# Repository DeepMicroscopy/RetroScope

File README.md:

<picture>
  <source media="(prefers-color-scheme: dark)" srcset="retroscope/qml/icons/app_logo_dark.png">
  <source media="(prefers-color-scheme: light)" srcset="retroscope/qml/icons/app_logo_light.png">
  
</picture>

---

**An Open Framework for Motorizing and Digitizing Vintage Microscopes**

RetroScope is an open-source framework for older analog microscopes. It combines software, digital imaging, motorized stage and focus control, calibration workflows, and adaptable mechanical parts so that existing microscopes can be upgraded instead of replaced.

The project was developed as part of the master's thesis **"Retrofitting a Vintage Microscope: Development of an Embedded System for Motorized Control and Digital Imaging"** in Applied Computer Science at Flensburg University of Applied Sciences.

## Overview

RetroScope is not just a single application. It is intended as a complete retrofit framework:

- **Control software**: Python/PySide6 backend with a QML touchscreen interface.
- **Embedded system**: Raspberry Pi-based embedded system with mock/development support for desktop.
- **Motor control**: XY stage and Z focus movement through a motor controller ([Sangaboard](https://build.openflexure.org/openflexure-microscope/v7.0.0-beta5/parts/electronics/sangaboard.html)).
- **Digital imaging**: Live camera preview, snapshots, video recording, OME-TIFF support and gallery management.
- **Automation**: Autofocus, focus stacking and tile scanning with stitching support.
- **REST API**: FastAPI with Swagger/OpenAPI documentation for e.g. external tools.
- **Calibration**: Calibration wizards with objective profiles, pixel scale, stage scale, backlash compensation, etc.
- **Electronics**: PCB schematics and Gerber files for manufacturing. Optional, just used to reduce the amount of cabling.
- **Mechanical design**: Parametric Fusion/CAD files and 3D-printable parts for adapting the retrofit to different microscopes.

## Features

- Low-latency live microscope view with overlays such as crosshair, scale bar and grid.
- Objective profile system for different magnifications and numerical apertures.
- Camera-assisted calibration for image scale, stage scale, and backlash compensation
- Manual stage and focus control through touchscreen, joystick, and configurable buttons.
- Contract-based autofocus.
- Automated focus stacks and tile scans.
- Measurement tools for distances, rectangles and angles.
- Gallery for snapshots, videos, focus stacks, scans, and tagging.
- REST API to access captures and trigger actions like autofocus.
- Configurable dark/light UI
- Mock mode for development without microscope hardware.

## Screenshots

## Software Architecture

The software is organized into modular layers:

- `retroscope/drivers`: Low-level hardware drivers for camera input, Sangaboard motor control, joystick ADC, buttons, and endstop.
- `retroscope/services`: Application logic for motion, autofocus, calibration, camera processing, tile scanning, focus stacking, updates, ...
- `retroscope/api`: FastAPI REST interface and OpenAPI/Swagger documentation.
- `retroscope/domain`: Pure domain modules (+ calculations) for scan planning, focus metrics, objective calibration, measurement, ...
- `retroscope/bridge`: Qt/PySide bridge objects that expose APIs to QML.
- `retroscope/qml`: Touchscreen user interface components and views.
- `tests`: Unit tests for calibration, autofocus, motion, scanning, settings, ...

This separation enables the expansion of individual subsystems without rewriting the entire platform.

## Hardware Recommendations

The following parts were used for the prototype:

- Raspberry Pi 4 Model B, 4 GB RAM
- [Sangaboard](https://build.openflexure.org/openflexure-microscope/v7.0.0-beta5/parts/electronics/sangaboard.html)
- 3x 28BYJ-48 Stepper Motors
- DSI Capacitive Touch Display
- Analog Joystick with 10k Potentiometers
- ADS1115 ADC Modul
- Incremental Rotary Encoder
- Bearing (60mm * 78mm * 10mm)
- Endstop
- 4x Buttons
- Various cables
- ABS (& PETG) filament/s for 3D printed parts
- Optional Custom PCB

## Installation

Clone the repository and create a virtual environment:

```bash
git clone https://github.com/marvincarstensen/RetroScope.git
cd retroscope
python[3] -m venv .venv
source .venv/bin/activate
pip install -r requirements.txt
```

For Raspberry Pi deployment, an additional setup script, to e.g. setup the service, has to be run with sudo:
```bash
sudo bash deploy/setup.sh
```

## Running

Start the application:

```bash
python app.py
```
> [!NOTE]
> First launch may take a little longer while Python builds its caches.

Run in mock mode for desktop env:

```bash
python app.py --mock
```

Enable development mode with QML hot reloading:

```bash
python app.py --mock --dev
```

Apply a UI scale factor:

```bash
python app.py --scale 1.5
```

On the Raspberry Pi with Wayland:

```bash
WAYLAND_DISPLAY=wayland-0 XDG_RUNTIME_DIR=/run/user/1000 python app.py --scale=1.5
```

## Testing

Run the test suite:

```bash
.venv/bin/python -m pytest -q
```

Compile-check on the package:

```bash
.venv/bin/python -m compileall -q retroscope
```

Run QML lint checks:

```bash
.venv/bin/pyside6-qmllint -I retroscope/qml $(find retroscope/qml -name '*.qml')
```

## Evaluation

The evaluations run inside the main application so they use the real camera pipeline, motion
services, calibration state, and workflow services. Results are written as CSV files to
`evaluation_output/`, with per-trial rows followed by summary rows. Needs a textured specimen and a safe stage position to run properly. The active objective needs to be selected and calibrated before running measurements.

Available evaluation types:

- `motion_accuracy`: compares commanded X/Y movement with measured image displacement and backlash residuals.
- `stage_scale`: measures repeated stage-scale estimates in micrometres per motor step.
- `calibration_repeat`: repeats stage-scale and backlash checks for the active objective.
- `workflow_reliability`: runs autofocus, focus stacking, and tile scanning through the app services.

Example runs:

```bash
python app.py --eval motion_accuracy --eval-arg axes=xy --eval-arg steps=100,200 --eval-arg reps=10
python app.py --eval stage_scale --eval-arg steps=100 --eval-arg reps=10
python app.py --eval calibration_repeat --eval-arg stage_steps=200 --eval-arg reps=10
python app.py --eval workflow_reliability --eval-arg reps=10 --eval-arg workflows=autofocus,focus_stacking,tile_scanning
```

## REST API

By default, the API is enabled and listens on port `8765`:

- `http://127.0.0.1:8765` / `http://<device-ip>:8765`
- Swagger UI: `http://<device-ip>:8765/docs`
- OpenAPI JSON: `http://<device-ip>:8765/openapi.json`

The current API is intentionally small and intended as an extension point for scripts, notebooks, and external tools.

Endpoint                                  | Description
------------------------------------------|-------------------------------
`GET /api/v1/health`                      | API health check.
`GET /api/v1/captures`                    | List gallery captures.
`GET /api/v1/captures/{id}/download`      | Download the original capture file.
`POST /api/v1/actions/autofocus`          | Start autofocus.
`POST /api/v1/actions/capture`            | Start capture.

## Demo Notebook

The repository contains a basic Jupyter notebook, `retroscope_api_demo.ipynb`, that demonstrates how to use the REST API.

## Shortcuts (Mock only)

The following keyboard shortcuts can be used in mock simulation:

Key       | Function           
----------|-------------------
WASD      | Joystick axes        
Space     | Joystick center (release)         
+/-       | Encoder step +-1       
1/2/3/4   | Button press 0–3      
E         | Simulate endstop triggered/released toggle

## Dependencies

The following plugins, libraries and frameworks are used:

Name                    | Version           
------------------------|-------------------
PySide6                 | 6.11.1
fastapi                 | 0.136.3
httpx2                  | 2.3.0
uvicorn                 | 0.49.0
numpy                   | 2.4.6
pytest                  | 9.0.3
opencv-python-headless  | 4.13.0.92
Pillow                  | 12.2.0
tifffile                | 2026.5.15
sangaboard              | 0.3.3
smbus2 (only on Pi)     | 0.6.1           
gpiod (only on Pi)      | 2.4.2   

## Additional Sources

- Font Awesome by Dave Gandy (https://fontawesome.com/)
- LateX Template, Logo & CI (DeepMicroscopy) by Nils Porsche

## Declaration: Use of Generative AI

The following generative AI tools were used in this thesis: 

- GitHub Copilot in VS Code was used for inline code-completion suggestions during implementation and writing.
- ChatGPT (OpenAI) & Claude (Anthropic) used to support brainstorming, quick research, and the generation of selected parts of the code (e.g. unit tests). AI-assisted scripts and functions are marked in the source code via comments.
- DeepL write (DeepL SE) were used in language editing and grammatical proof-reading.

All AI-generated material was critically reviewed, edited, and verified by the author. No generative AI system was used to produce original scientific results, experimental data, proofs, or final implementations of algorithms. The author assumes full responsibility for the content, correctness, and originality of this thesis.

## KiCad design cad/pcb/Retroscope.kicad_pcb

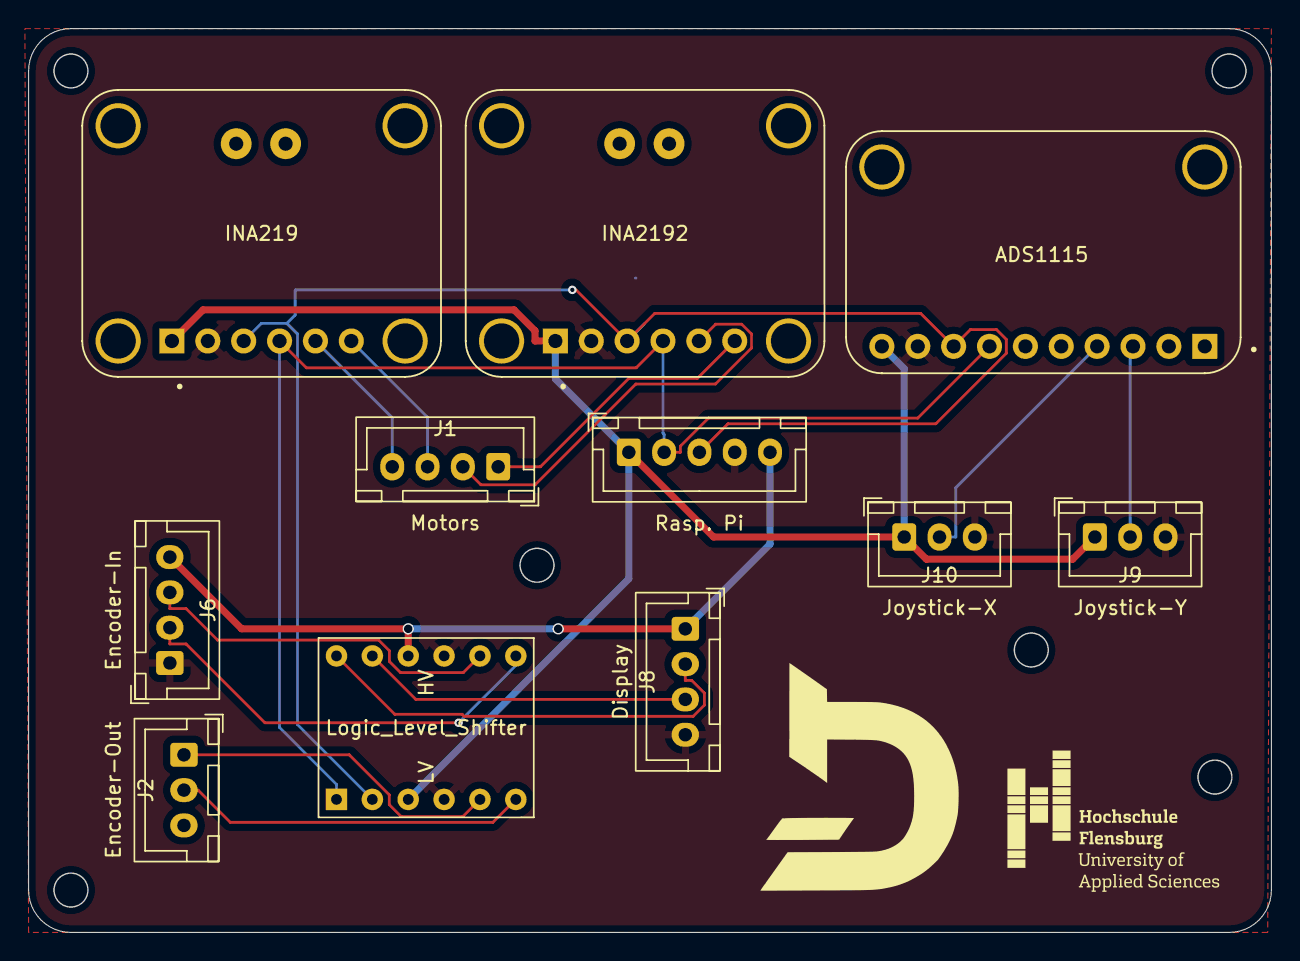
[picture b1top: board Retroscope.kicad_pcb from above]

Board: 2 copper layers, 88.0 x 64.0 mm, 11 parts (0 on the bottom side), 19 nets.

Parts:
A1: Logic_Level_Shifter; LogicLevelConverter_Module
ADS1115: ZC261500; MODULE_ZC261500
INA219, INA2192: INA219; MODULE_INA219
J1: Motors; JST_XH_B4B-XH-A_1x04_P2.50mm_Vertical
J2: Encoder-Out; JST_XH_B3B-XH-A_1x03_P2.50mm_Vertical
J6: Encoder-In; JST_XH_B4B-XH-A_1x04_P2.50mm_Vertical
J7: Rasp. Pi; JST_XH_B5B-XH-A_1x05_P2.50mm_Vertical
J8: Display; JST_XH_B4B-XH-A_1x04_P2.50mm_Vertical
J9: Joystick-Y; JST_XH_B3B-XH-A_1x03_P2.50mm_Vertical
J10: Joystick-X; JST_XH_B3B-XH-A_1x03_P2.50mm_Vertical

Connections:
+3.3V: A1.3 (LV), ADS1115.10 (VDD), INA219.1 (VCC), INA2192.1 (VCC), J7.1, J9.1, J10.1
+5V: A1.10 (HV), J6.4, J7.5, J8.1
GND: A1.4 (GND), A1.9 (GND), ADS1115.9 (GND), INA219.2 (GND), INA2192.2 (GND), J6.1, J7.4, J8.4, J9.3, J10.3
unnamed: A1.12 (HV1), J8.2
unnamed: A1.11 (HV2), J8.3
unnamed: A1.8 (HV3), J6.3
unnamed: A1.7 (HV4), J6.2
unnamed: A1.1 (LV1), ADS1115.7 (SDA), INA219.4 (SDA), INA2192.4 (SDA), J7.2
unnamed: A1.2 (LV2), ADS1115.8 (SCL), INA219.3 (SCL), INA2192.3 (SCL), J7.3
unnamed: A1.5 (LV3), J2.1
unnamed: A1.6 (LV4), J2.2
unnamed: INA2192.6 (VIN+), INA2192.VIN+, J1.1
unnamed: INA2192.5 (VIN-), INA2192.VIN-, J1.2
unnamed: INA219.6 (VIN+), INA219.VIN+, J1.3
unnamed: INA219.5 (VIN-), INA219.VIN-, J1.4
unnamed: ADS1115.3 (A1), J9.2
unnamed: ADS1115.4 (A0), J10.2
unnamed: INA2192.SH1 (SHIELD), INA2192.SH2 (SHIELD), INA2192.SH3 (SHIELD), INA2192.SH4 (SHIELD)
unnamed: INA219.SH1 (SHIELD), INA219.SH2 (SHIELD), INA219.SH3 (SHIELD), INA219.SH4 (SHIELD)

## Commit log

2026-06-03 Migrated repo to "RetroScope"
2026-06-03 Refactoring, dead-code cleanup, general cleanup
2026-06-04 Added logos, photos
2026-06-04 Added dependencies, installation, etc. to README.md
2026-06-04 Featres, overview, hardware, ... for README.md
2026-06-04 Added screenshot section placeholder
2026-06-04 Added rest-api placeholder
2026-06-05 New keyboard shortcut for encoder step
2026-06-05 Implemented debug toggles for frame analysis and live preview
2026-06-05 Reworked frame analysis to run on separte thread
2026-06-05 Adjusted joystick sample timeout
2026-06-05 Improve autofocus frame freshness
2026-06-05 Trying to fix the autofocus freshness issue
2026-06-05 Copying frame for processing to free up main thread
2026-06-05 Switching from dynamic joystick smoothing to fixed command dispatch
2026-06-05 Fixed AF canceling
2026-06-05 Implemented camera reconnect logic
2026-06-05 Added guard for button events during new video device change
2026-06-05 Reworked the camera reconnect logic
2026-06-05 Added noise supression on gpio buttons
2026-06-05 Added an no camera placeholder in live view
2026-06-05 Added option to save as grid mosaic, not just as a fallback
2026-06-05 Added backlash visu in live view sidebar
2026-06-06 Adjused height and flipped y axis
2026-06-06 Fixed video recording after camera pipeline rework
2026-06-06 Moved video recording to native qt record
2026-06-06 Implemented non-blocking move for video recording
2026-06-06 Removed bookmark logic
2026-06-06 Refactored/Reorganized tests
2026-06-06 "Reset defaults" not resets the whole config not just the active objective
2026-06-06 Restart after config reset
2026-06-06 Updated defaults
2026-06-06 Added joystick backlash compensation
2026-06-06 Testing flatfield correction and positional stiching
2026-06-06 Removed flat field correction
2026-06-06 Reworked gallery with thumbnails, caches and lazy loading
2026-06-06 Grid view to full container width
2026-06-06 Increased gallery grid view size
2026-06-06 Fixed detail view image crop
2026-06-06 Hopefully fixed tap-to-move overshoot
2026-06-06 Reworked tap-to-move by calc frame pixels to steps
2026-06-06 Use frame tap size in tap-to-move calc
2026-06-06 Added logo to top left corner of statusbar
2026-06-07 Fixed qml issues
2026-06-07 Prep gallery for api
2026-06-07 Prepared dependencies for rest api
2026-06-07 Implemented REST API
2026-06-07 Added REST API demo jupyter notebook
2026-06-07 Fixed remaining warnings/errors in the log during runtime
2026-06-07 Fixed capture count in disk stats
2026-06-07 Polished views, texts, icons, etc.
2026-06-07 Reset notebook state
2026-06-08 Added pcb files and fusion model
2026-06-08 Extended rest api with capture action endpoint
2026-06-08 Protect joystick backlash compensation moves from coalescing
2026-06-08 Replaced logo
2026-06-08 Added evaluation runner and experiments
2026-06-09 Trying to fix remaining log warnings
2026-06-09 Fixing motion eval
2026-06-09 Fixing calibration eval
2026-06-09 Increased settle time and add fresh frame grab for eval
2026-06-09 Harden evaluations
2026-06-09 Removed manual pixel-scale evaluation
2026-06-09 Removed measurement and gallery eval workflows
2026-06-09 Added active objective metadata to eval results
2026-06-09 Increased AF timeout in eval
2026-06-09 Updated sangaboard driver to separate blocking and query moves with protected flag
2026-06-11 Added evaluation results
2026-06-16 First draft
2026-06-16 Removed drill file reference
2026-06-19 Added additional screenshot and photos
2026-06-19 Final thesis correction pass
2026-06-19 MICCAI latex template
2026-06-19 First paper draft
2026-06-19 Made sure that no modification to the paper latex template were made
2026-06-19 Added addtional figures to the paper
2026-06-21 Changes to paper content
2026-06-22 Updated dates
2026-06-23 Next paper iteration
2026-06-23 Merged figures for paper
2026-06-25 Removed weekly pdf and updated paper
2026-06-25 Removed Workflow Reliability subsection from paper
2026-06-29 Updated readme for paper submission
2026-06-30 Finalizing paper
